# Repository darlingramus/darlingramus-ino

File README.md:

# darlingramus-ino

My attempt to build my own arduino-like board

## schematic

## 3D model

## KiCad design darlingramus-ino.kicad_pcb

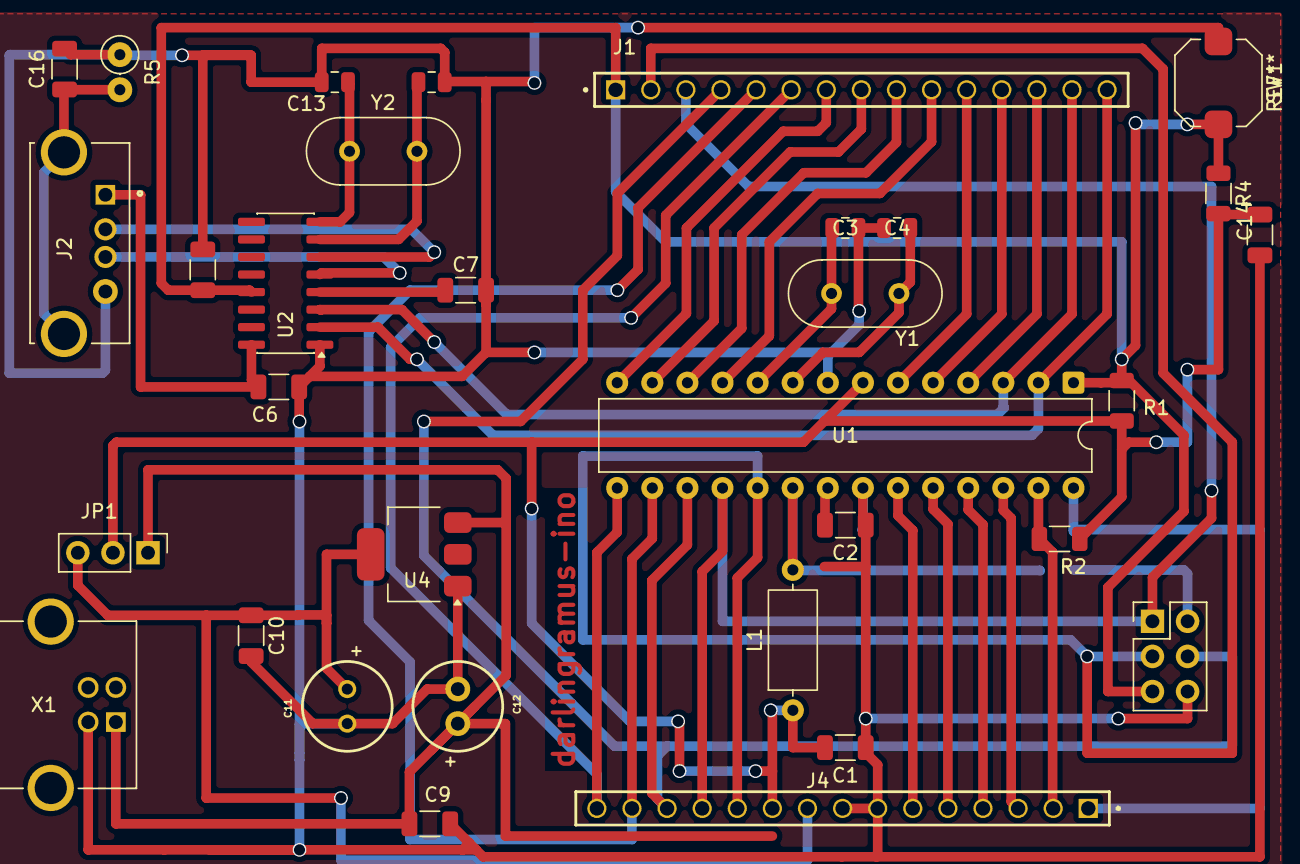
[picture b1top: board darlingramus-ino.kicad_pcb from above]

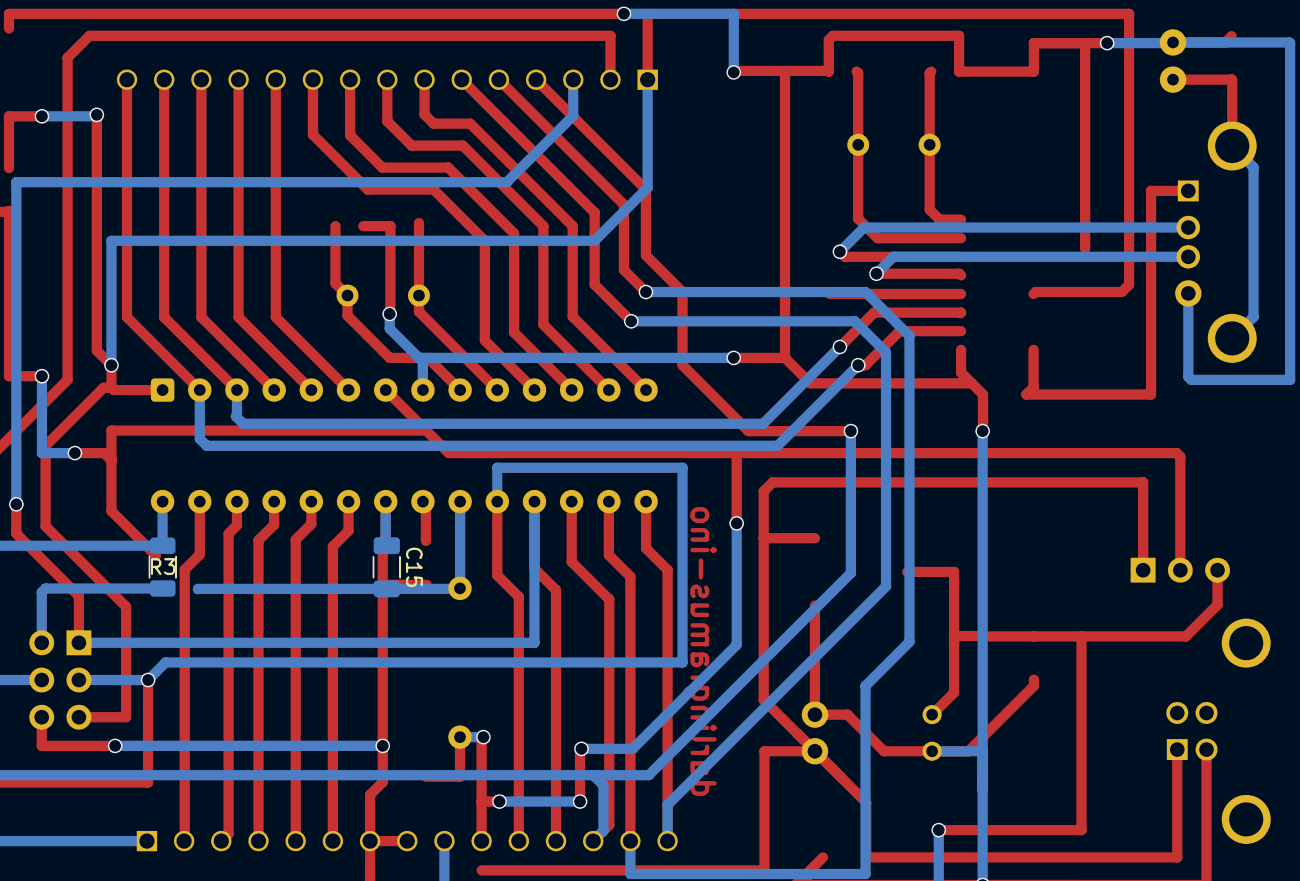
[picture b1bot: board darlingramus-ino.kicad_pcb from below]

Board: 2 copper layers, 34 parts (2 on the bottom side), 36 nets.

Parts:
C1, C2, C6, C7, C8, C9, C10, C14, C15, C16: 100nF; C_1206_3216Metric
C3, C4, C5, C13: 22pF; C_0805_2012Metric
C11: 10uF; 100uFCap_MOD
C12: 100 uF; 100uFCap_MOD
J1, J4: SSW-115-03-G-S_LG; SAMTEC_SSW-115-03-G-S
J2: USB-A1VSB6_LG; ONSHORE_USB-A1VSB6
J3: Header2x3_LG; PinHeader_2x03_P2.54mm_Vertical
JP1: Jumper_3_Open; PinHeader_1x03_P2.54mm_Vertical
L1: 10uH; L_Axial_L7.0mm_D3.3mm_P10.16mm_Horizontal_Fastron_MICC
R1: 10kΩ; R_1206_3216Metric
R2, R3: 4,7kΩ; R_1206_3216Metric
R4: 220 Ω; R_1206_3216Metric
R5: 1MΩ; R_Axial_DIN0207_L6.3mm_D2.5mm_P2.54mm_Vertical
SW1: SW_Push; SW_Push_1TS009xxxx-xxxx-xxxx_6x6x5mm
U1: ATmega328-P; DIP-28_W7.62mm
U2: CH340G; SOIC-16_3.9x9.9mm_P1.27mm
U4: AMS1117-3.3; SOT-223-3_TabPin2
X1: USB-B1HSB6_LG; OST_USB-B1HSB6
Y1: 16 MHz; Crystal_HC49-U_Vertical
Y2: 12 MHz; Crystal_HC49-U_Vertical

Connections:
+5V: C1.2, C6.2, C14.2, J2.1 (VUSB), J3.2, J4.10, JP1.2 (C), L1.1, R1.2, R2.2, R3.2, R4.2, U1.7 (VCC), U2.16 (VCC)
A0: J4.06, U1.23 (PC0)
A1: J4.05, U1.24 (PC1)
A2: J4.04, U1.25 (PC2)
A3: J4.03, U1.26 (PC3)
A4 (SDA): J4.02, R2.1, U1.27 (PC4)
A5 (SCL): J4.01, R3.1, U1.28 (PC5)
D0 (RX): J1.15, U1.2 (PD0), U2.2 (TXD)
D1 (TX): J1.14, U1.3 (PD1), U2.3 (RXD)
D2: J1.13, U1.4 (PD2)
D3 ~: J1.12, U1.5 (PD3)
D4: J1.11, U1.6 (PD4)
D5 ~: J1.10, U1.11 (PD5)
D6 ~: J1.09, U1.12 (PD6)
D7: J1.08, U1.13 (PD7)
D8: J1.07, U1.14 (PB0)
D9 ~: J1.06, J4.15, U1.15 (PB1)
D10 ~: J1.05, J4.14, U1.16 (PB2)
GND: C1.1, C2.2, C3.2, C4.2, C5.2, C6.1, C7.2, C8.2, C9.2, C10.2, C11.2, C12.2, C13.2, C14.1, C15.1, C16.1, J2.4 (GND), J3.6, J4.07, J4.08, R5.1, SW1.1, U1.8 (GND), U1.22 (GND), U2.1 (GND), U4.1 (GND), X1.4 (GND)
MISO: J1.03, J3.1, J4.12, U1.18 (PB4)
MOSI ~: J1.04, J3.4, J4.13, U1.17 (PB3)
unnamed: C16.2, J2.S1 (SHIELD), J2.S2 (SHIELD), R5.2
unnamed: J2.1 (VUSB), U2.5 (UD+)
unnamed: J2.2 (D-), U2.6 (UD-)
unnamed: C9.1, C12.1, JP1.1 (A), U4.3 (VI), X1.1 (VCC)
unnamed: C10.1, C11.1, JP1.3 (B), U4.2 (VO)
unnamed: R4.1, SW1.2
unnamed: C2.1, U1.21 (AREF)
unnamed: C15.2, L1.2, U1.20 (AVCC)
unnamed: C7.1, U2.4 (V3)
RES: C8.1, J1.01, J3.5, R1.1, U1.1 (~RESET/PC6), U2.13 (~DTR)
SCK: J1.02, J3.3, J4.11, U1.19 (PB5)
XATL1: C4.1, U1.9 (XTAL1/PB6), Y1.2
XATL2: C3.1, U1.10 (XTAL2/PB7), Y1.1
XATL11: C13.1, U2.8 (XO), Y2.1
XATL22: C5.1, U2.7 (XI), Y2.2

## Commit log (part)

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2026-06-15 Schematic and full pcb
